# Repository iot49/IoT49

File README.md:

# Electronics for IoT

* Code for IoT devices in MicroPython and derivatives
* Documentation (Jupyter Notebooks)

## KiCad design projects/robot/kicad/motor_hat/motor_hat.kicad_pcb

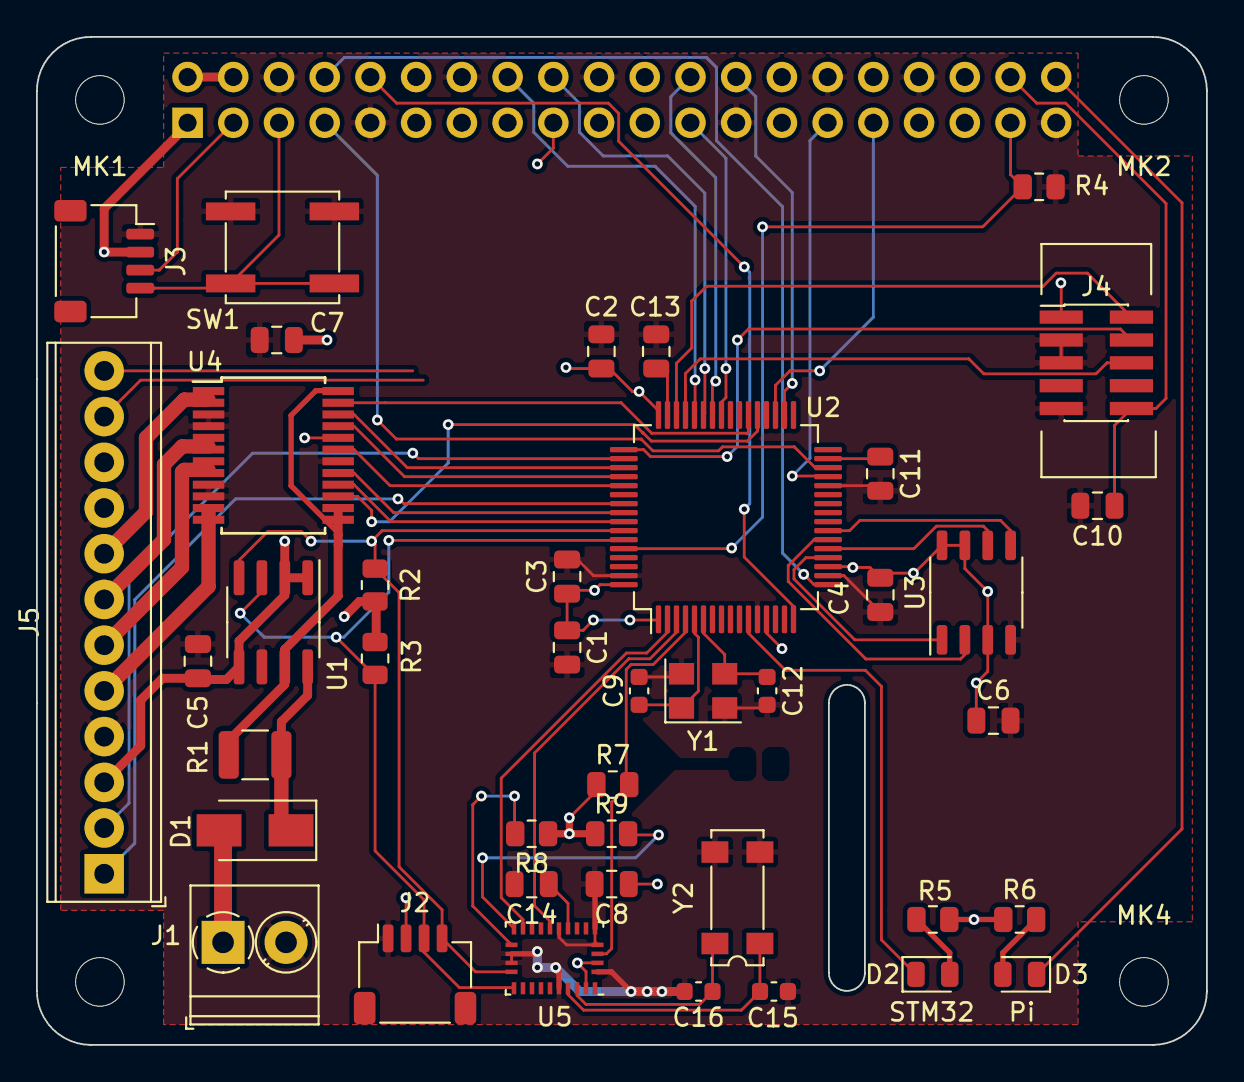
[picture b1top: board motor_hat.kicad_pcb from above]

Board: 2 copper layers, 65.0 x 56.0 mm, 46 parts (1 on the bottom side), 60 nets.

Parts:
C1, C11, C13: 10u; C_0805_2012Metric
C2, C3: 1u; C_0805_2012Metric
C4, C5, C6, C7, C8, C10, C14: 100n; C_0805_2012Metric
C9, C12, C15, C16: 22p; C_0603_1608Metric
D1: MBRA340; D_SMA
D2: RED; LED_0805_2012Metric
D3: GREEN; LED_0805_2012Metric
J1: Screw_Terminal_01x02; TerminalBlock_Phoenix_PT-1,5-2-3.5-H_1x02_P3.50mm_Horizontal
J2, J3: Conn_01x04; JST_SH_SM04B-SRSS-TB_1x04-1MP_P1.00mm_Horizontal
J4: Conn_02x05_Odd_Even; SWD_PinHeader_2x05_P1.27mm_Vertical_SMD
J5: Screw_Terminal_01x12; TerminalBlock_Phoenix_MPT-0,5-12-2.54_1x12_P2.54mm_Horizont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
MK1, MK2, MK3, MK4: M2.5; MountingHole_2.7mm_M2.5
P1: Conn_02x20_Odd_Even; PinSocket_2x20_P2.54mm_Vertical
R1: 0.1; R_1210_3225Metric
R2, R3: 4.7k; R_0805_2012Metric
R4: 100k; R_0805_2012Metric
R5, R6: 1k; R_0805_2012Metric
R7, R8, R9: 10k; R_0805_2012Metric
SW1: SW_Push; SW_SPST_EVPBF
U1: INA219BxD; SOIC-8_3.9x4.9mm_P1.27mm
U2: STM32F405RGTx; LQFP-64_10x10mm_P0.5mm
U3: S25FL128LAGMFI013; SOP-8_3.9x4.9mm_P1.27mm
U4: TB6612FNG; SSOP-24_5.3x8.2mm_P0.65mm
U5: BNO085; LGA-28_5.2x3.8mm_P0.5mm
Y1: 12MHz; Crystal_SMD_SeikoEpson_FA238V-4Pin_3.2x2.5mm
Y2: 32kHz; Crystal_SMD_SeikoEpson_MC156-4Pin_7.1x2.5mm

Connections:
!IMU_BOOT: R7.2, U2.4, U5.4
!IMU_RESET: U2.3, U5.11
!RESET: C10.1, J4.10, P1.38, U2.7
!STBY: U2.53, U4.19
+3V3: C1.1, C2.1, C3.1, C4.1, C5.1, C6.1, C7.1, C8.1, J2.2, J3.2, J4.1, J5.3, J5.10, P1.1, P1.17, R2.1, R3.1, R5.1, R6.1, R7.1, R8.1, R9.1, U1.1, U1.2, U1.5, U2.1, U2.13, U2.19, U2.32, U2.48, U2.64, U3.3, U3.7, U3.8, U4.20, U5.3, U5.28
+5V: P1.2, P1.4
+12V: R1.2, U1.7, U4.13, U4.14, U4.24
/CAP: C14.1, U5.9
/PH0: C9.1, U2.5, Y1.1
/PH1: C12.1, U2.6, Y1.3
/VCAP_1: C11.1, U2.31
/VCAP_2: C13.1, U2.47
/Vin1: D1.2, J1.1
/Vin2: D1.1, R1.1, U1.8
/XI32: C16.1, U5.27, Y2.4
/XO32: C15.1, U5.26, Y2.1
AIN1: U2.52, U4.21
AIN2: U2.51, U4.22
AO1: J5.8, U4.1, U4.2
AO2: J5.7, U4.5, U4.6
BIN1: U2.56, U4.17
BIN2: U2.57, U4.16
BO1: J5.5, U4.11, U4.12
BO2: J5.6, U4.7, U4.8
BOOT0: P1.37, R4.1, U2.60
ENC_A1: J5.2, U2.50
ENC_A2: J5.1, U2.55
ENC_B1: J5.11, U2.14
ENC_B2: J5.12, U2.15
FLASH_CS: U2.20, U3.1
FLASH_MISO: U2.22, U3.2
FLASH_MOSI: U2.23, U3.5
FLASH_SCK: U2.21, U3.6
GND: C1.2, C2.2, C3.2, C4.2, C5.2, C6.2, C7.2, C8.2, C9.2, C10.2, C11.2, C12.2, C13.2, C14.2, C15.2, C16.2, J1.2, J2.1, J3.1, J4.3, J4.5, J4.9, J5.4, J5.9, P1.6, P1.9, P1.14, P1.20, P1.25, P1.30, P1.34, P1.39, R4.2, SW1.2, U1.6, U2.12, U2.18, U2.28, U2.63, U3.4, U4.3, U4.4, U4.9, U4.10, U4.18, U5.2, U5.5, U5.6, U5.10, U5.17, U5.18, U5.25, Y1.2, Y1.4, Y2.2, Y2.3
IMU_INT: U2.2, U5.14
LED: D2.1, U2.11
unnamed: D2.2, R5.2
unnamed: D3.2, R6.2
unnamed: R8.2, U5.16
unnamed: R9.2, U5.15
PI4_CTS: P1.31, U2.35
PI4_RTS: P1.26, U2.34
PI4_RX: P1.29, U2.29
PI4_TX: P1.7, U2.30
PI_LED: D3.1, P1.40
PI_RX: P1.10, U2.16
PI_SCL: J3.4, P1.5, SW1.1
PI_SDA: J3.3, P1.3
PI_TX: P1.8, U2.17
PI_X1: P1.23, U2.41
PI_X2: P1.24, U2.42
PI_X3: P1.18, U2.43
PI_X4: P1.16, U2.44
PWMA: U2.38, U4.23
PWMB: U2.37, U4.15
SCL: J2.4, R2.2, U1.4, U2.58, U5.19
SDA: J2.3, R3.2, U1.3, U2.59, U5.20
SWCLK: J4.4, U2.49
SWDIO: J4.2, U2.46
SWO: J4.6, U2.45

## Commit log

2021-03-15 pi initial
2021-03-16 add projects folder, update pi/bin
2021-03-16 add boards/
2021-03-16 bin/idf.py - esp32 ide with docker
2021-03-22 update pi install
2021-03-22 jupyter iot-kernel docs
2021-04-07 countless updates
2021-05-20 balena
2021-05-20 boards
2021-05-20 config doc snippets test
2021-05-20 projects
